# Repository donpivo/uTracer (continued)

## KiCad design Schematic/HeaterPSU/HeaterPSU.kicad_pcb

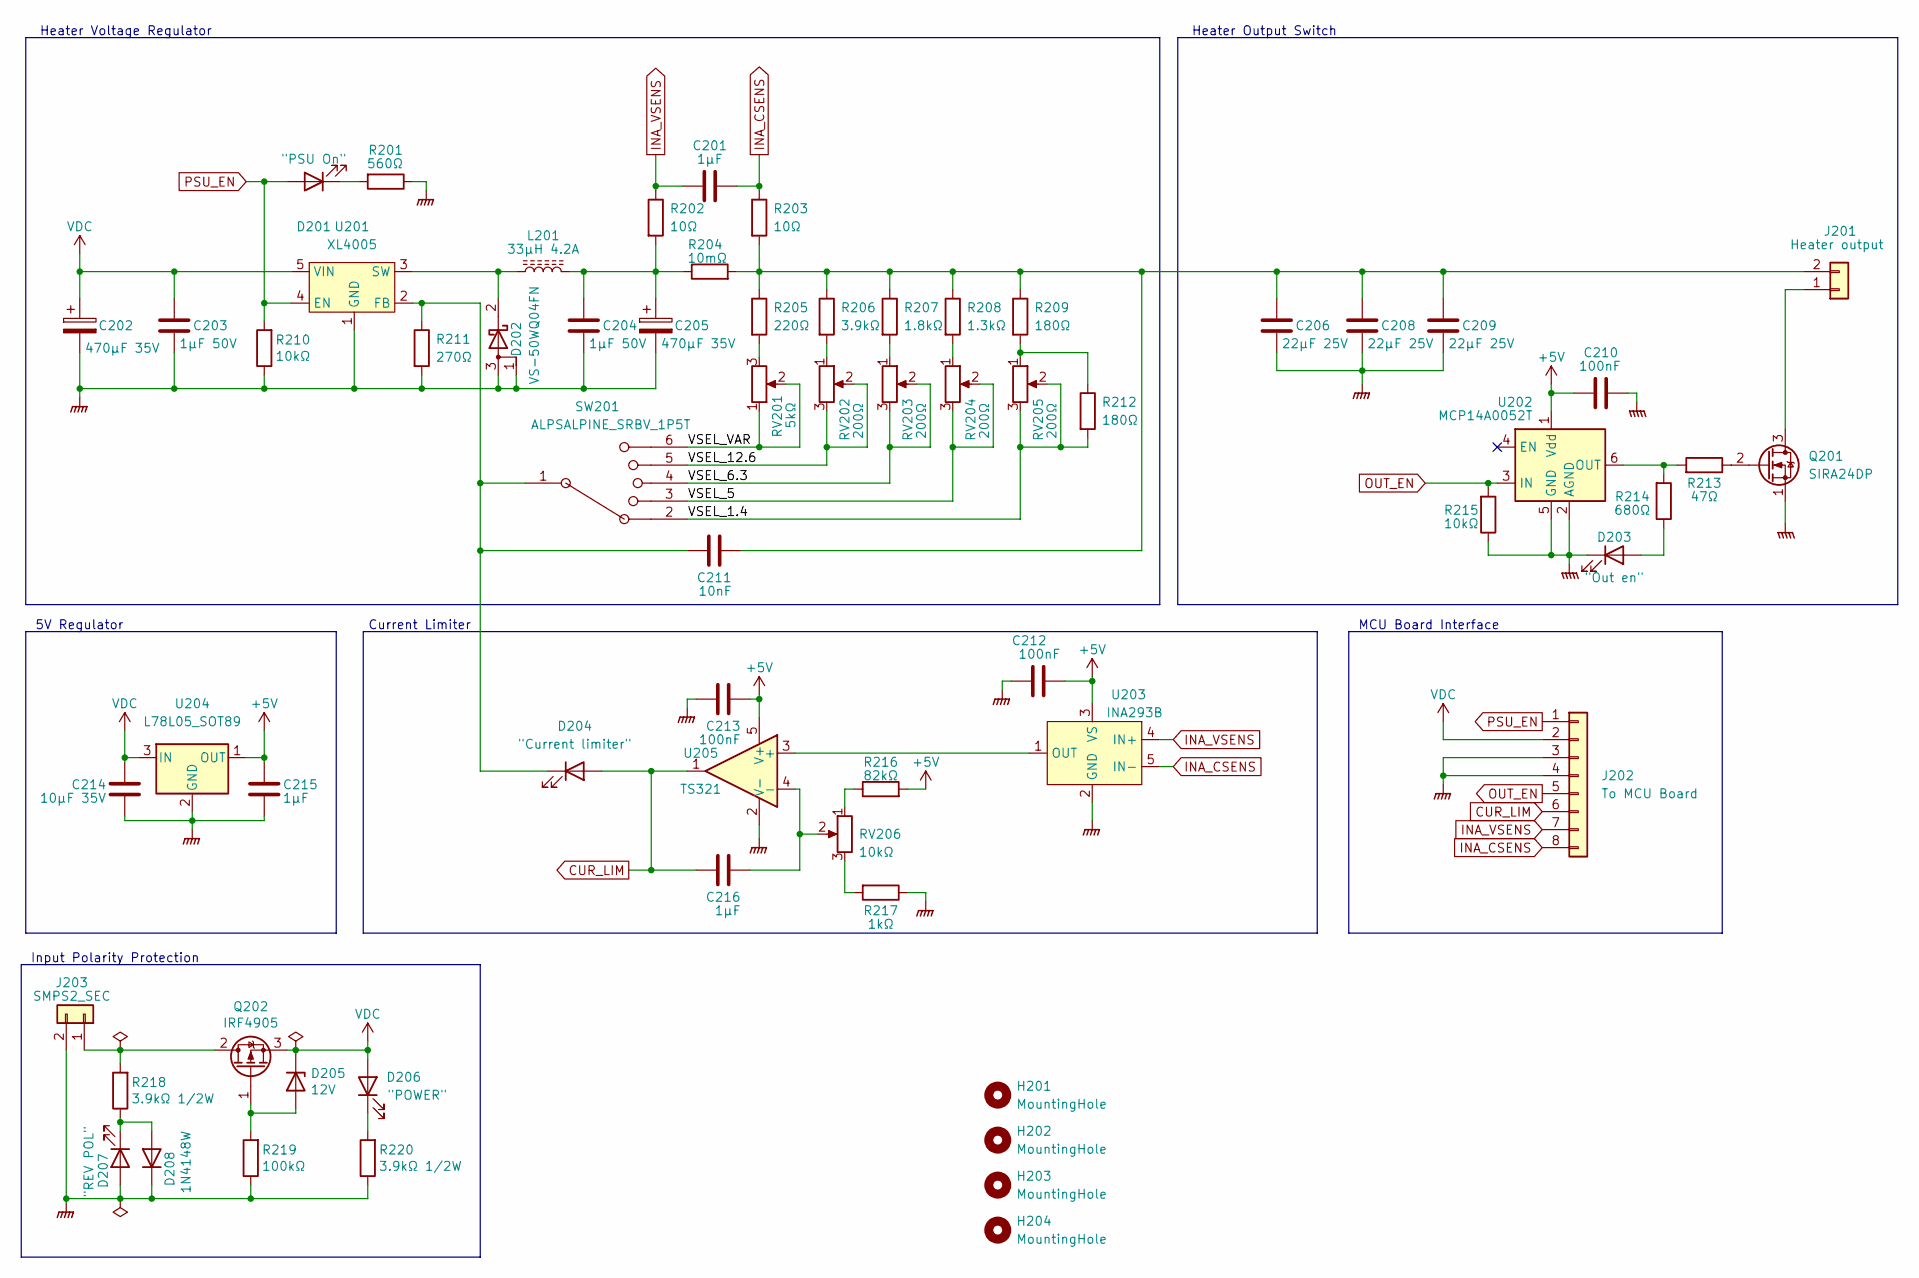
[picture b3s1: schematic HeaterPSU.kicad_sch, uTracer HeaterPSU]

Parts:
C201, C215, C216: 1µF; C_0603_1608Metric_Pad1.08x0.95mm_HandSolder
C202, C205: 470µF 35V; CP_Elec_8x10
C203, C204: 1µF 50V; C_0805_2012Metric_Pad1.18x1.45mm_HandSolder
C206, C208, C209: 22µF 25V; C_0805_2012Metric_Pad1.18x1.45mm_HandSolder
C210, C212, C213: 100nF; C_0603_1608Metric_Pad1.08x0.95mm_HandSolder
C211: 10nF; C_0805_2012Metric_Pad1.18x1.45mm_HandSolder
C214: 10µF 35V; C_0603_1608Metric_Pad1.08x0.95mm_HandSolder
D201: "PSU On"; LED_0603_1608Metric_Pad1.05x0.95mm_HandSolder
D202: VS-50WQ04FN; TO-252-2
D203: "Out en"; LED_0603_1608Metric_Pad1.05x0.95mm_HandSolder
D204: "Current limiter"; LED_0603_1608Metric_Pad1.05x0.95mm_HandSolder
D205: 12V; D_SOD-123
D206: "POWER"; LED_0603_1608Metric_Pad1.05x0.95mm_HandSolder
D207: "REV POL"; LED_0603_1608Metric_Pad1.05x0.95mm_HandSolder
D208: 1N4148W; D_SOD-123
H201, H202, H203, H204: MountingHole; MountingHole_3.2mm_M3
J201: Heater output; TerminalBlock_LCSC_P5.08mm
J202: To MCU Board; PinSocket_1x08_P2.54mm_Vertical
J203: SMPS2_SEC; TerminalBlock_LCSC_P5.08mm
L201: 33µH 4.2A; L_12x12mm_H8mm
Q201: SIRA24DP; SIRA24DP-T1-GE3
Q202: IRF4905; TO-263-2
R201: 560Ω; R_0603_1608Metric_Pad0.98x0.95mm_HandSolder
R202, R203: 10Ω; R_0805_2012Metric_Pad1.20x1.40mm_HandSolder
R204: 10mΩ; R_2512_6332Metric_Pad1.40x3.35mm_HandSolder
R205: 220Ω; R_0805_2012Metric_Pad1.20x1.40mm_HandSolder
R206: 3.9kΩ; R_0805_2012Metric_Pad1.20x1.40mm_HandSolder
R207: 1.8kΩ; R_0805_2012Metric_Pad1.20x1.40mm_HandSolder
R208: 1.3kΩ; R_0805_2012Metric_Pad1.20x1.40mm_HandSolder
R209, R212: 180Ω; R_0805_2012Metric_Pad1.20x1.40mm_HandSolder
R210: 10kΩ; R_0805_2012Metric_Pad1.20x1.40mm_HandSolder
R211: 270Ω; R_0805_2012Metric_Pad1.20x1.40mm_HandSolder
R213: 47Ω; R_0603_1608Metric_Pad0.98x0.95mm_HandSolder
R214: 680Ω; R_0603_1608Metric_Pad0.98x0.95mm_HandSolder
R215: 10kΩ; R_0603_1608Metric_Pad0.98x0.95mm_HandSolder
R216: 82kΩ; R_0603_1608Metric_Pad0.98x0.95mm_HandSolder
R217: 1kΩ; R_0603_1608Metric_Pad0.98x0.95mm_HandSolder
R218, R220: 3.9kΩ 1/2W; R_1210_3225Metric_Pad1.30x2.65mm_HandSolder
R219: 100kΩ; R_0805_2012Metric_Pad1.20x1.40mm_HandSolder
RV201: 5kΩ; Potentiometer_Bourns_PTV09A-1_Single_Vertical
RV202, RV203, RV204, RV205: 200Ω; Potentiometer_TT_35W
RV206: 10kΩ; Potentiometer_Bourns_PTV09A-1_Single_Vertical
SW201: ALPSALPINE_SRBV_1P5T; SRBV141404
U201: XL4005; TO-263-5_TabPin3
U202: MCP14A0052T; SOT-23-6_Handsoldering
U203: INA293B; SOT-23-5_HandSoldering
U204: L78L05_SOT89; SOT-89-3
U205: TS321; SOT-23-5_HandSoldering

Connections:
+5V: C210.2, C212.2, C213.2, C215.2, R216.2, U202.1 (Vdd), U203.3 (VS), U204.1 (OUT), U205.5 (V+)
/VSEL_1.4: R212.2, RV205.2, RV205.3, SW201.2
/VSEL_5: RV204.2, RV204.3, SW201.3
/VSEL_6.3: RV203.2, RV203.3, SW201.4
/VSEL_12.6: RV202.2, RV202.3, SW201.5
/VSEL_VAR: RV201.1, RV201.2, SW201.6
CUR_LIM: C216.1, D204.2 (A), J202.6, U205.1
GNDPWR: C202.2, C203.2, C204.2, C205.2, C206.2, C208.2, C209.2, C210.1, C212.1, C213.1, C214.1, C215.1, D202.1 (A), D202.3 (A), D203.1 (K), D207.2 (A), D208.1 (K), J202.3, J202.4, J203.2, Q201.1 (S), R201.1, R210.1, R211.2, R215.1, R217.1, R219.1, R220.1, U201.1 (GND), U202.2 (AGND), U202.5 (GND), U203.2 (GND), U204.2 (GND), U205.2 (V-)
INA_CSENS: C201.1, J202.8, R203.1, U203.5 (IN-)
INA_VSENS: C201.2, J202.7, R202.1, U203.4 (IN+)
unnamed: C204.1, C205.1, L201.2, R202.2, R204.1
unnamed: C211.1, D204.1 (K), R211.1, SW201.1, U201.2 (FB)
unnamed: C206.1, C208.1, C209.1, C211.2, J201.2, R203.2, R204.2, R205.1, R206.1, R207.1, R208.1, R209.1
unnamed: C216.2, RV206.2, U205.4 (-)
unnamed: D201.1 (K), R201.2
unnamed: D202.2 (K), L201.1, U201.3 (SW)
unnamed: D203.2 (A), R214.1
unnamed: D205.2 (A), Q202.1 (G), R219.2
unnamed: D206.1 (K), R220.2
unnamed: D207.1 (K), D208.2 (A), R218.1
unnamed: J201.1, Q201.3 (D)
unnamed: J203.1, Q202.2 (D), R218.2
unnamed: Q201.2 (G), R213.1
unnamed: R205.2, RV201.3
unnamed: R206.2, RV202.1
unnamed: R207.2, RV203.1
unnamed: R208.2, RV204.1
unnamed: R209.2, R212.1, RV205.1
unnamed: R213.2, R214.2, U202.6 (OUT)
unnamed: R216.1, RV206.1
unnamed: R217.2, RV206.3
unnamed: U203.1 (OUT), U205.3 (+)
OUT_EN: J202.5, R215.2, U202.3 (IN)
PSU_EN: D201.2 (A), J202.1, R210.2, U201.4 (EN)
VDC: C202.1, C203.1, C214.2, D205.1 (K), D206.2 (A), J202.2, Q202.3 (S), U201.5 (VIN), U204.3 (IN)

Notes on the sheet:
MCU Board Interface
5V Regulator
Heater Voltage Regulator
Input Polarity Protection
Current Limiter
Heater Output Switch

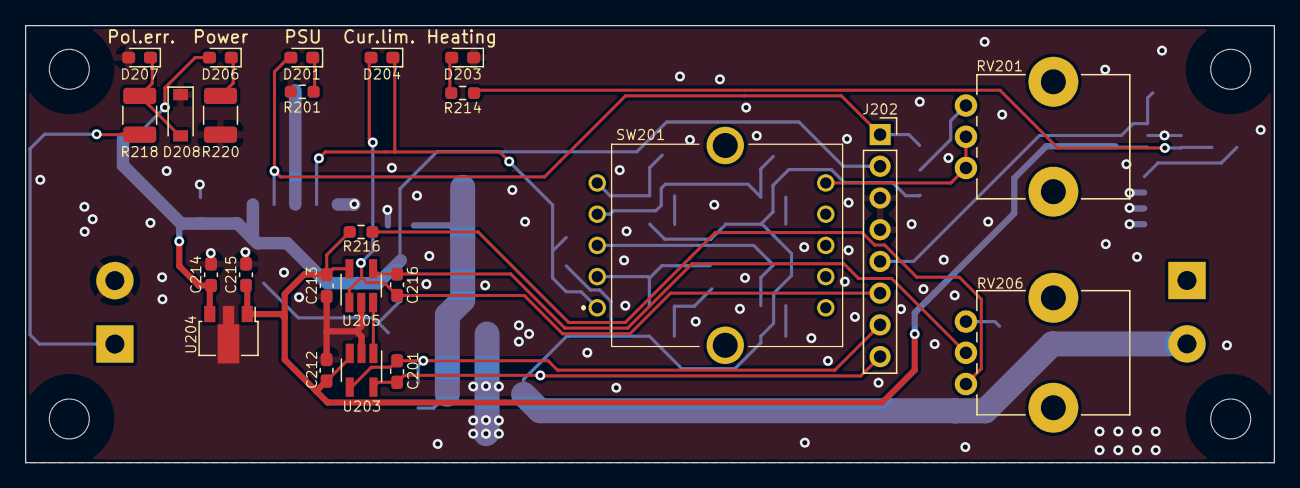
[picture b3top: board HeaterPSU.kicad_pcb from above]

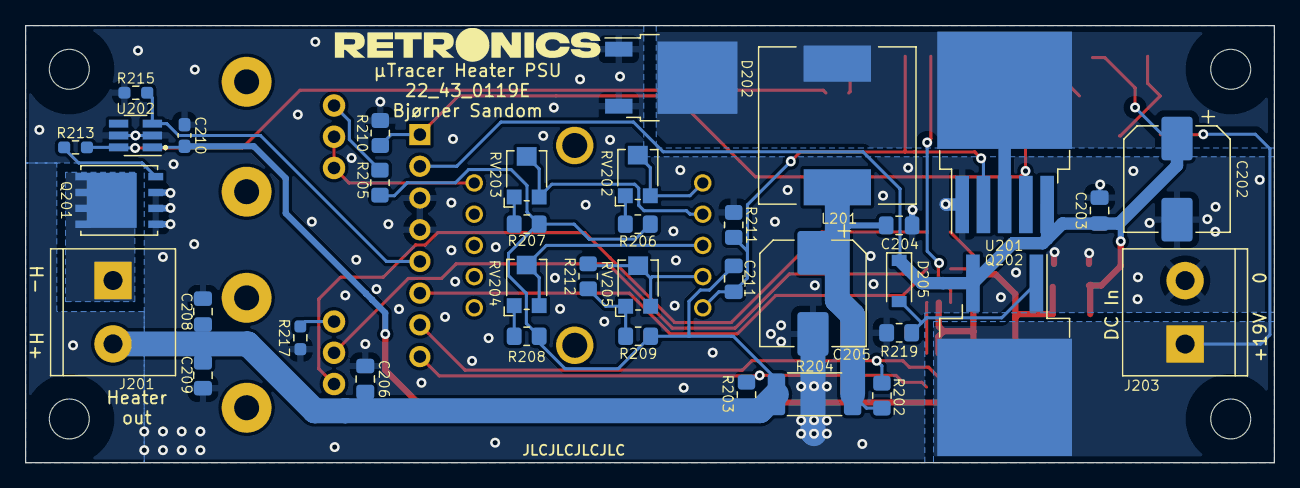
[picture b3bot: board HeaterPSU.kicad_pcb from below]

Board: 2 copper layers, 100.0 x 35.0 mm, 65 parts (37 on the bottom side), 35 nets.

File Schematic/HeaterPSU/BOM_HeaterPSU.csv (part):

"Source:","C:\Users\bjorn\OneDrive\Projects\µTracer\Schematic\HeaterPSU\HeaterPSU.kicad_sch"
"Date:","Fri May 12 07:55:15 2023"
"Tool:","Eeschema (6.0.11)"
"Generator:","C:\Program Files\KiCad\6.0\bin\scripting\plugins/bom_csv_grouped_by_value.py"
"Component Count:","65"

"Individual Components:"

"Item","Qty","Reference(s)","Value","LibPart","Footprint","Datasheet"
"","","C201","1µF","Device:C","Capacitor_SMD:C_0603_1608Metric_Pad1.08x0.95mm_HandSolder","~"
"","","C202","470µF 35V","Device:C_Polarized","Capacitor_SMD:CP_Elec_8x10","~"
"","","C203","1µF 50V","Device:C","Capacitor_SMD:C_0805_2012Metric_Pad1.18x1.45mm_HandSolder","~"
"","","C204","1µF 50V","Device:C","Capacitor_SMD:C_0805_2012Metric_Pad1.18x1.45mm_HandSolder","~"
"","","C205","470µF 35V","Device:C_Polarized","Capacitor_SMD:CP_Elec_8x10","~"
"","","C206","22µF 25V","Device:C","Capacitor_SMD:C_0805_2012Metric_Pad1.18x1.45mm_HandSolder","~"
"","","C208","22µF 25V","Device:C","Capacitor_SMD:C_0805_2012Metric_Pad1.18x1.45mm_HandSolder","~"
"","","C209","22µF 25V","Device:C","Capacitor_SMD:C_0805_2012Metric_Pad1.18x1.45mm_HandSolder","~"
"","","C210","100nF","Device:C","Capacitor_SMD:C_0603_1608Metric_Pad1.08x0.95mm_HandSolder","~"
"","","C211","10nF","Device:C","Capacitor_SMD:C_0805_2012Metric_Pad1.18x1.45mm_HandSolder","~"
"","","C212","100nF","Device:C","Capacitor_SMD:C_0603_1608Metric_Pad1.08x0.95mm_HandSolder","~"
"","","C213","100nF","Device:C","Capacitor_SMD:C_0603_1608Metric_Pad1.08x0.95mm_HandSolder","~"
"","","C214","10µF 35V","Device:C","Capacitor_SMD:C_0603_1608Metric_Pad1.08x0.95mm_HandSolder","~"
"","","C215","1µF","Device:C","Capacitor_SMD:C_0603_1608Metric_Pad1.08x0.95mm_HandSolder","~"
"","","C216","1µF","Device:C","Capacitor_SMD:C_0603_1608Metric_Pad1.08x0.95mm_HandSolder","~"
"","","D201","""PSU On""","Device:LED","LED_SMD:LED_0603_1608Metric_Pad1.05x0.95mm_HandSolder","~"
"","","D202","VS-50WQ04FN","myDevices:D_Schottky_VS-50WQ04FN","Package_TO_SOT_SMD:TO-252-2","~"
"","","D203","""Out en""","Device:LED","LED_SMD:LED_0603_1608Metric_Pad1.05x0.95mm_HandSolder","~"
"","","D204","""Current limiter""","Device:LED","LED_SMD:LED_0603_1608Metric_Pad1.05x0.95mm_HandSolder","~"
"","","D205","12V","Device:D_Zener","Diode_SMD:D_SOD-123","~"
"","","D206","""POWER""","Device:LED","LED_SMD:LED_0603_1608Metric_Pad1.05x0.95mm_HandSolder","~"
"","","D207","""REV POL""","Device:LED","LED_SMD:LED_0603_1608Metric_Pad1.05x0.95mm_HandSolder","~"
"","","D208","1N4148W","Diode:1N4148W","Diode_SMD:D_SOD-123","https://www.vishay.com/docs/85748/1n4148w.pdf"
"","","H201","MountingHole","Mechanical:MountingHole","MountingHole:MountingHole_3.2mm_M3","~"
"","","H202","MountingHole","Mechanical:MountingHole","MountingHole:MountingHole_3.2mm_M3","~"
"","","H203","MountingHole","Mechanical:MountingHole","MountingHole:MountingHole_3.2mm_M3","~"
"","","H204","MountingHole","Mechanical:MountingHole","MountingHole:MountingHole_3.2mm_M3","~"
"","","J201","Heater output","Connector_Generic:Conn_01x02","myDevices:TerminalBlock_LCSC_P5.08mm","~"
"","","J202","To MCU Board","Connector_Generic:Conn_01x08","Connector_PinSocket_2.54mm:PinSocket_1x08_P2.54mm_Vertical","~"
"","","J203","SMPS2_SEC","Connector_Generic:Conn_01x02","myDevices:TerminalBlock_LCSC_P5.08mm","~"
"","","L201","33µH 4.2A","Device:L_Ferrite","Inductor_SMD:L_12x12mm_H8mm","~"
"","","Q201","SIRA24DP","myDevices:SIRA24DP-T1-GE3","myDevices:SIRA24DP-T1-GE3",""
"","","Q202","IRF4905","Transistor_FET:IRF4905","Package_TO_SOT_SMD:TO-263-2","http://www.infineon.com/dgdl/irf4905.pdf?fileId=5546d4625336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"
"","","R201","560Ω","Device:R","Resistor_SMD:R_0603_1608Metric_Pad0.98x0.95mm_HandSolder","~"
"","","R202","10Ω","Device:R","Resistor_SMD:R_0805_2012Metric_Pad1.20x1.40mm_HandSolder","~"
"","","R203","10Ω","Device:R","Resistor_SMD:R_0805_2012Metric_Pad1.20x1.40mm_HandSolder","~"
"","","R204","10mΩ","Device:R","Resistor_SMD:R_2512_6332Metric_Pad1.40x3.35mm_HandSolder","~"
"","","R205","220Ω","Device:R","Resistor_SMD:R_0805_2012Metric_Pad1.20x1.40mm_HandSolder","~"
"","","R206","3.9kΩ","Device:R","Resistor_SMD:R_0805_2012Metric_Pad1.20x1.40mm_HandSolder","~"
"","","R207","1.8kΩ","Device:R","Resistor_SMD:R_0805_2012Metric_Pad1.20x1.40mm_HandSolder","~"
"","","R208","1.3kΩ","Device:R","Resistor_SMD:R_0805_2012Metric_Pad1.20x1.40mm_HandSolder","~"
"","","R209","180Ω","Device:R","Resistor_SMD:R_0805_2012Metric_Pad1.20x1.40mm_HandSolder","~"
"","","R210","10kΩ","Device:R","Resistor_SMD:R_0805_2012Metric_Pad1.20x1.40mm_HandSolder","~"
"","","R211","270Ω","Device:R","Resistor_SMD:R_0805_2012Metric_Pad1.20x1.40mm_HandSolder","~"
"","","R212","180Ω","Device:R","Resistor_SMD:R_0805_2012Metric_Pad1.20x1.40mm_HandSolder","~"
"","","R213","47Ω","Device:R","Resistor_SMD:R_0603_1608Metric_Pad0.98x0.95mm_HandSolder","~"
"","","R214","680Ω","Device:R","Resistor_SMD:R_0603_1608Metric_Pad0.98x0.95mm_HandSolder","~"
"","","R215","10kΩ","Device:R","Resistor_SMD:R_0603_1608Metric_Pad0.98x0.95mm_HandSolder","~"
"","","R216","91kΩ","Device:R","Resistor_SMD:R_0603_1608Metric_Pad0.98x0.95mm_HandSolder","~"
"","","R217","1kΩ","Device:R","Resistor_SMD:R_0603_1608Metric_Pad0.98x0.95mm_HandSolder","~"
"","","R218","5.6kΩ 1/2W","Device:R","Resistor_SMD:R_1210_3225Metric_Pad1.30x2.65mm_HandSolder","~"
"","","R219","100kΩ","Device:R","Resistor_SMD:R_0805_2012Metric_Pad1.20x1.40mm_HandSolder","~"
"","","R220","5.6kΩ 1/2W","Device:R","Resistor_SMD:R_1210_3225Metric_Pad1.30x2.65mm_HandSolder","~"
"","","RV201","5kΩ","Device:R_Potentiometer","Potentiometer_THT:Potentiometer_Bourns_PTV09A-1_Single_Vertical","~"
"","","RV202","200Ω","Device:R_Potentiometer","Potentiometer_SMD:Potentiometer_TT_35W","~"
"","","RV203","200Ω","Device:R_Potentiometer","Potentiometer_SMD:Potentiometer_TT_35W","~"
"","","RV204","200Ω","Device:R_Potentiometer","Potentiometer_SMD:Potentiometer_TT_35W","~"
"","","RV205","200Ω","Device:R_Potentiometer","Potentiometer_SMD:Potentiometer_TT_35W","~"
"","","RV206","10kΩ","Device:R_Potentiometer","Potentiometer_THT:Potentiometer_Bourns_PTV09A-1_Single_Vertical","~"
"","","SW201","ALPSALPINE SRBV150901","myDevices:SW_Rotary_1P5T_ALPSALPINE_SRBV","myDevices:SRBV141404",""
"","","U201","XL4005","myDevices:XL4005","Package_TO_SOT_SMD:TO-263-5_TabPin3",""
"","","U202","MCP14A0052T","myDevices:MCP14A0052T","Package_TO_SOT_SMD:SOT-23-6_Handsoldering",""
"","","U203","INA293B","myDevices:INA293B","Package_TO_SOT_SMD:SOT-23-5_HandSoldering",""
"","","U204","L78L05_SOT89","Regulator_Linear:L78L05_SOT89","Package_TO_SOT_SMD:SOT-89-3","http://www.st.com/content/ccc/resource/technical/document/da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"
"","","U205","TS321","myDevices:RS8751","Package_TO_SOT_SMD:SOT-23-5_HandSoldering",""



"Collated Components:"

"Item","Qty","Reference(s)","Value","LibPart","Footprint","Datasheet"
"1","3","C201, C215, C216","1µF","Device:C","Capacitor_SMD:C_0603_1608Metric_Pad1.08x0.95mm_HandSolder","~"
"2","2","C202, C205","470µF 35V","Device:C_Polarized","Capacitor_SMD:CP_Elec_8x10","~"
"3","2","C203, C204","1µF 50V","Device:C","Capacitor_SMD:C_0805_2012Metric_Pad1.18x1.45mm_HandSolder","~"
"4","3","C206, C208, C209","22µF 25V","Device:C","Capacitor_SMD:C_0805_2012Metric_Pad1.18x1.45mm_HandSolder","~"
"5","3","C210, C212, C213","100nF","Device:C","Capacitor_SMD:C_0603_1608Metric_Pad1.08x0.95mm_HandSolder","~"
"6","1","C211","10nF","Device:C","Capacitor_SMD:C_0805_2012Metric_Pad1.18x1.45mm_HandSolder","~"
"7","1","C214","10µF 35V","Device:C","Capacitor_SMD:C_0603_1608Metric_Pad1.08x0.95mm_HandSolder","~"
"8","1","D201","""PSU On""","Device:LED","LED_SMD:LED_0603_1608Metric_Pad1.05x0.95mm_HandSolder","~"
"9","1","D202","VS-50WQ04FN","myDevices:D_Schottky_VS-50WQ04FN","Package_TO_SOT_SMD:TO-252-2","~"
"10","1","D203","""Out en""","Device:LED","LED_SMD:LED_0603_1608Metric_Pad1.05x0.95mm_HandSolder","~"
"11","1","D204","""Current limiter""","Device:LED","LED_SMD:LED_0603_1608Metric_Pad1.05x0.95mm_HandSolder","~"
"12","1","D205","12V","Device:D_Zener","Diode_SMD:D_SOD-123","~"
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
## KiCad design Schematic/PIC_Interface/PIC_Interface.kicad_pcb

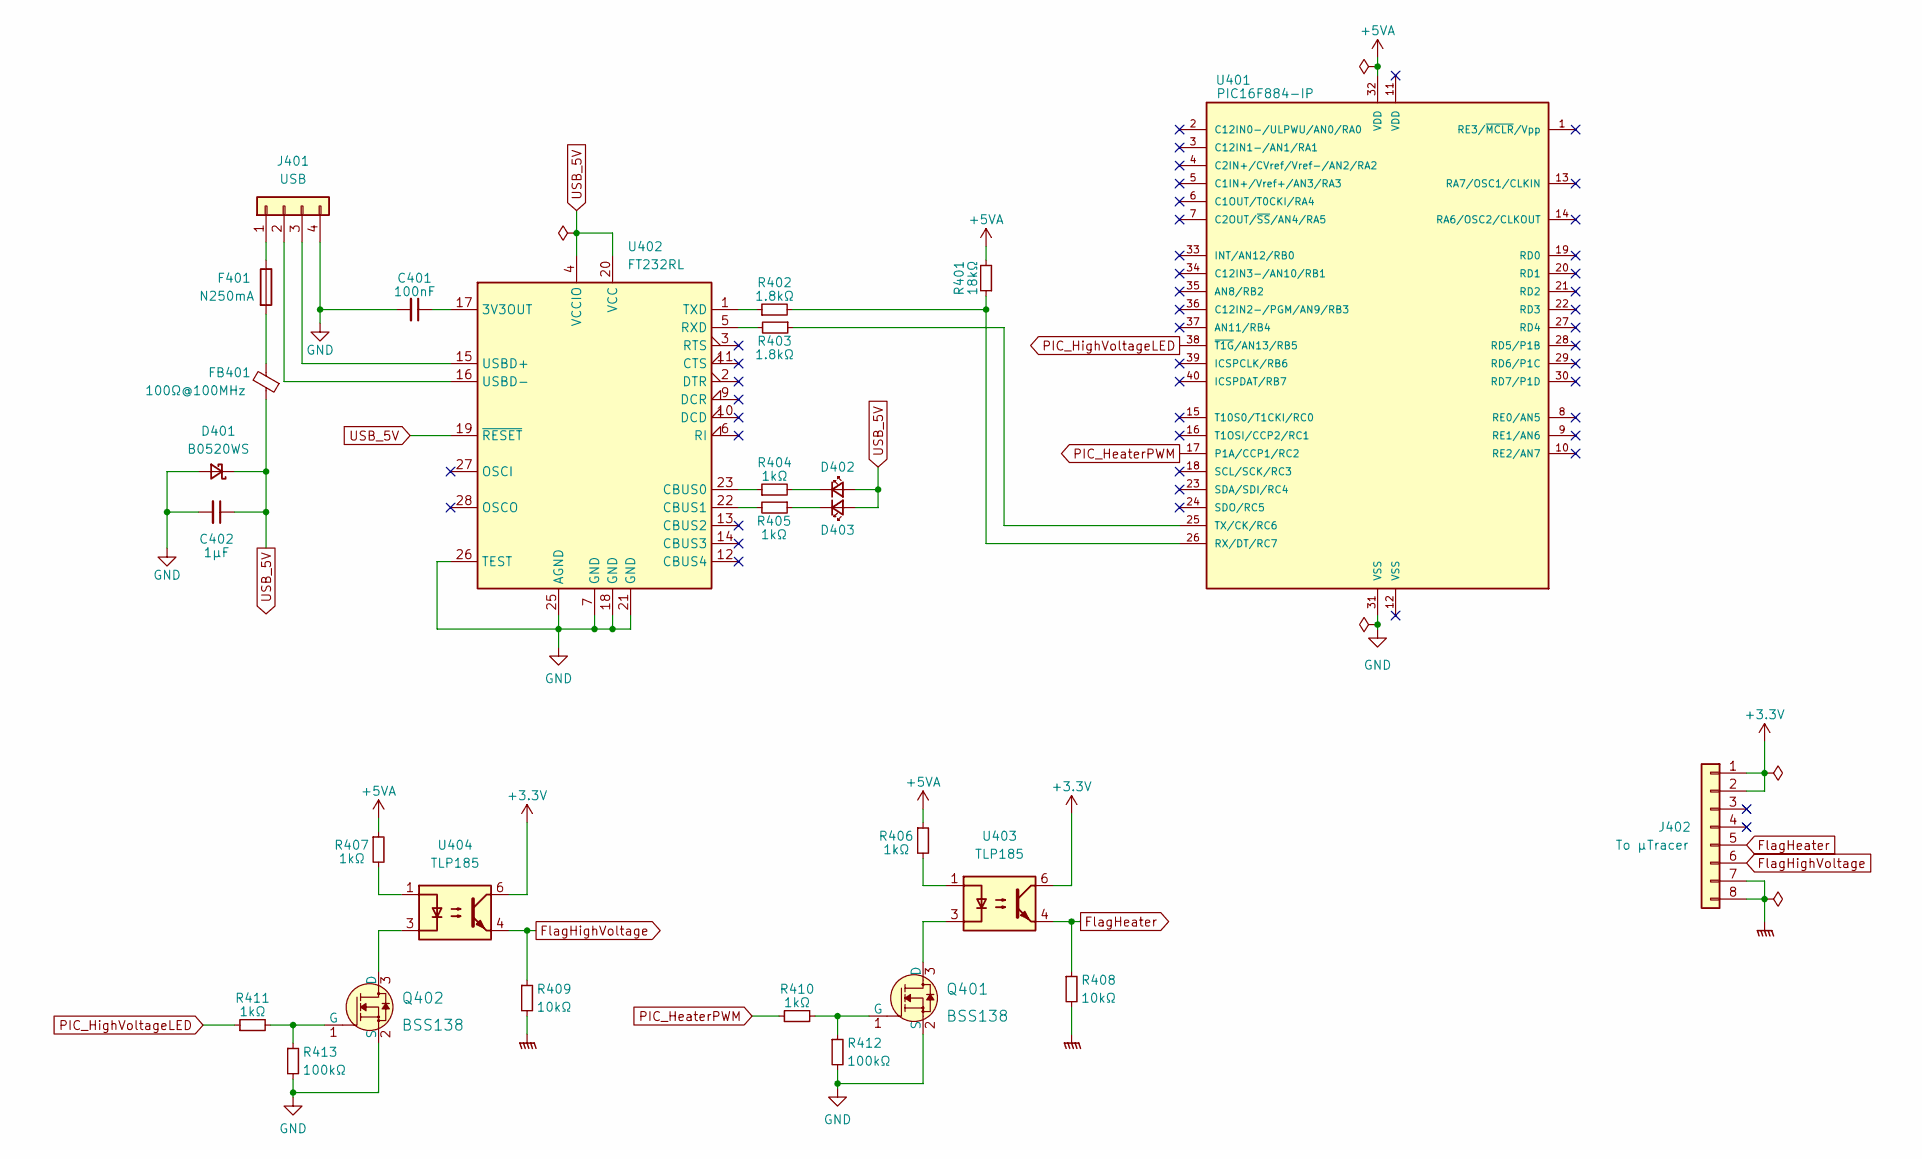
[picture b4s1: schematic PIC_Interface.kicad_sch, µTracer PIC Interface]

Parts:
C401: 100nF; C_0603_1608Metric_Pad1.08x0.95mm_HandSolder
C402: 1µF; C_0603_1608Metric_Pad1.08x0.95mm_HandSolder
D401: B0520WS; D_SOD-323_HandSoldering
D402, D403: LED_Small; LED_0603_1608Metric_Pad1.05x0.95mm_HandSolder
F401: N250mA; Fuse_1206_3216Metric_Pad1.42x1.75mm_HandSolder
FB401: 100Ω@100MHz; L_0603_1608Metric_Pad1.05x0.95mm_HandSolder
J401: USB; KF2510-4P
J402: To µTracer; 0527450897
Q401, Q402: BSS138; SOT-23-3; MPN BSS138; Digi-Key_PN BSS138CT-ND
R401: 18kΩ; R_0603_1608Metric_Pad0.98x0.95mm_HandSolder
R402, R403: 1.8kΩ; R_0603_1608Metric_Pad0.98x0.95mm_HandSolder
R404, R405, R406, R407, R410, R411: 1kΩ; R_0603_1608Metric_Pad0.98x0.95mm_HandSolder
R408, R409: 10kΩ; R_0603_1608Metric_Pad0.98x0.95mm_HandSolder
R412, R413: 100kΩ; R_0603_1608Metric_Pad0.98x0.95mm_HandSolder
U401: PIC16F884-IP; DIP-40_W15.24mm_Socket_ThroughPCB
U402: FT232RL; SSOP-28_5.3x10.2mm_P0.65mm
U403, U404: TLP185; SOIC-4_4.55x3.7mm_P2.54mm

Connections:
+3V3: J402.1, J402.2, U403.6, U404.6
+5VA: R401.2, R406.1, R407.1, U401.32 (VDD)
FlagHeater: J402.5, R408.1, U403.4
FlagHighVoltage: J402.6, R409.1, U404.4
GND: C401.2, C402.2, D401.2 (A), J401.4, Q401.2 (S), Q402.2 (S), R412.2, R413.2, U401.31 (VSS), U402.7 (GND), U402.18 (GND), U402.21 (GND), U402.25 (AGND), U402.26 (TEST)
GNDPWR: J402.7, J402.8, R408.2, R409.2
unnamed: C401.1, U402.17 (3V3OUT)
unnamed: D402.1 (K), R404.2
unnamed 8: D403.1 (K), R405.1; also elsewhere on the board
unnamed: F401.1, J401.1
unnamed: F401.2, FB401.2
unnamed: J401.2, U402.16 (USBD-)
unnamed: J401.3, U402.15 (USBD+)
unnamed: Q401.1 (G), R410.2, R412.1
unnamed: Q401.3 (D), U403.3
unnamed: Q402.1 (G), R411.2, R413.1
unnamed: Q402.3 (D), U404.3
unnamed: R401.1, R402.2, U401.26 (RX/DT/RC7)
unnamed: R402.1, U402.1 (TXD)
unnamed: R403.1, U401.25 (TX/CK/RC6)
unnamed: R403.2, U402.5 (RXD)
unnamed: R404.1, U402.23 (CBUS0)
unnamed: R405.2, U402.22 (CBUS1)
unnamed: R406.2, U403.1
unnamed: R407.2, U404.1
PIC_HeaterPWM: R410.1, U401.17 (P1A/CCP1/RC2)
PIC_HighVoltageLED: R411.1, U401.38 (~T1G/AN13/RB5)
USB_5V: C402.1, D401.1 (K), D402.2 (A), D403.2 (A), FB401.1, U402.4 (VCCIO), U402.19 (~RESET), U402.20 (VCC); also elsewhere on the board

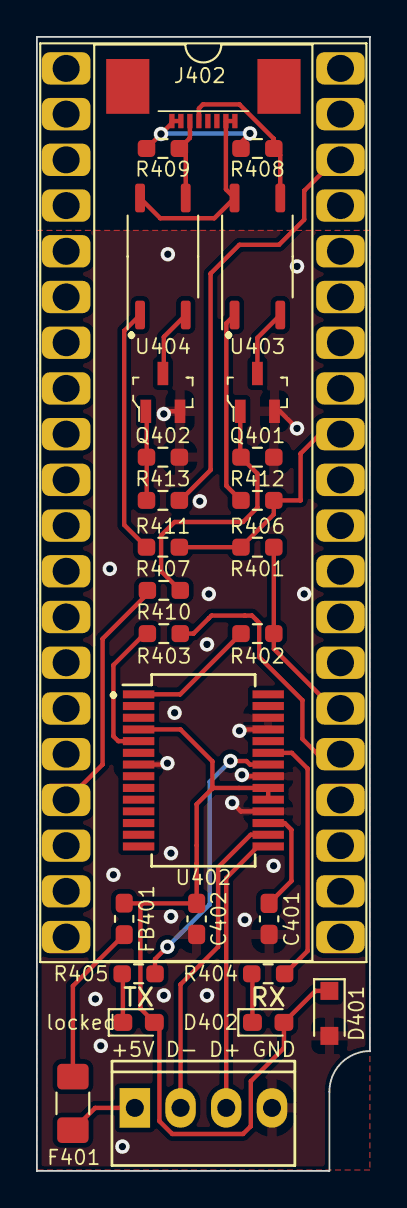
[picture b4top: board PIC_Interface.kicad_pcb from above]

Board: 2 copper layers, 18.5 x 63.0 mm, 28 parts (0 on the bottom side), 28 nets.

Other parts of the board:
locked: LED_Small; LED_0603_1608Metric_Pad1.05x0.95mm_HandSolder

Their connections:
unnamed 8: locked.1 (K); also elsewhere on the board
USB_5V: locked.2 (A); also elsewhere on the board

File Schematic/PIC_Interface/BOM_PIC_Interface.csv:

"Source:","C:\Users\bjorn\OneDrive\Projects\µTracer\Schematic\PIC_Interface\PIC_Interface.kicad_sch"
"Date:","Fri May 12 08:04:09 2023"
"Tool:","Eeschema (6.0.11)"
"Generator:","C:\Program Files\KiCad\6.0\bin\scripting\plugins/bom_csv_grouped_by_value.py"
"Component Count:","28"

"Individual Components:"

"Item","Qty","Reference(s)","Value","LibPart","Footprint","Datasheet","Category","DK_Datasheet_Link","DK_Detail_Page","Description","Digi-Key_PN","Family","MPN","Manufacturer","Status"
"","","C401","100nF","Device:C_Small","Capacitor_SMD:C_0603_1608Metric_Pad1.08x0.95mm_HandSolder","~","","","","","","","","",""
"","","C402","1µF","Device:C_Small","Capacitor_SMD:C_0603_1608Metric_Pad1.08x0.95mm_HandSolder","~","","","","","","","","",""
"","","D401","B0520WS","Device:D_Schottky_Small","Diode_SMD:D_SOD-323_HandSoldering","~","","","","","","","","",""
"","","D402","LED_Small","Device:LED_Small","LED_SMD:LED_0603_1608Metric_Pad1.05x0.95mm_HandSolder","~","","","","","","","","",""
"","","D403","LED_Small","Device:LED_Small","LED_SMD:LED_0603_1608Metric_Pad1.05x0.95mm_HandSolder","~","","","","","","","","",""
"","","F401","N250mA","Device:Fuse","Fuse:Fuse_1206_3216Metric_Pad1.42x1.75mm_HandSolder","~","","","","","","","","",""
"","","FB401","100Ω@100MHz","Device:FerriteBead_Small","Inductor_SMD:L_0603_1608Metric_Pad1.05x0.95mm_HandSolder","~","","","","","","","","",""
"","","J401","USB","Connector_Generic:Conn_01x04","myDevices:KF2510-4P","~","","","","","","","","",""
"","","J402","To heater module","Connector_Generic:Conn_01x08","myDevices:0527450897","~","","","","","","","","",""
"","","Q401","BSS138","dk_Transistors-FETs-MOSFETs-Single:BSS138","digikey-footprints:SOT-23-3","https://www.onsemi.com/pub/Collateral/BSS138-D.PDF","Discrete Semiconductor Products","https://www.onsemi.com/pub/Collateral/BSS138-D.PDF","/product-detail/en/on-semiconductor/BSS138/BSS138CT-ND/244294","MOSFET N-CH 50V 220MA SOT-23","BSS138CT-ND","Transistors - FETs, MOSFETs - Single","BSS138","ON Semiconductor","Active"
"","","Q402","BSS138","dk_Transistors-FETs-MOSFETs-Single:BSS138","digikey-footprints:SOT-23-3","https://www.onsemi.com/pub/Collateral/BSS138-D.PDF","Discrete Semiconductor Products","https://www.onsemi.com/pub/Collateral/BSS138-D.PDF","/product-detail/en/on-semiconductor/BSS138/BSS138CT-ND/244294","MOSFET N-CH 50V 220MA SOT-23","BSS138CT-ND","Transistors - FETs, MOSFETs - Single","BSS138","ON Semiconductor","Active"
"","","R401","18kΩ","Device:R_Small","Resistor_SMD:R_0603_1608Metric_Pad0.98x0.95mm_HandSolder","~","","","","","","","","",""
"","","R402","1.8kΩ","Device:R_Small","Resistor_SMD:R_0603_1608Metric_Pad0.98x0.95mm_HandSolder","~","","","","","","","","",""
"","","R403","1.8kΩ","Device:R_Small","Resistor_SMD:R_0603_1608Metric_Pad0.98x0.95mm_HandSolder","~","","","","","","","","",""
"","","R404","1kΩ","Device:R_Small","Resistor_SMD:R_0603_1608Metric_Pad0.98x0.95mm_HandSolder","~","","","","","","","","",""
"","","R405","1kΩ","Device:R_Small","Resistor_SMD:R_0603_1608Metric_Pad0.98x0.95mm_HandSolder","~","","","","","","","","",""
"","","R406","220Ω","Device:R_Small","Resistor_SMD:R_0603_1608Metric_Pad0.98x0.95mm_HandSolder","~","","","","","","","","",""
"","","R407","1kΩ","Device:R_Small","Resistor_SMD:R_0603_1608Metric_Pad0.98x0.95mm_HandSolder","~","","","","","","","","",""
"","","R408","10kΩ","Device:R_Small","Resistor_SMD:R_0603_1608Metric_Pad0.98x0.95mm_HandSolder","~","","","","","","","","",""
"","","R409","10kΩ","Device:R_Small","Resistor_SMD:R_0603_1608Metric_Pad0.98x0.95mm_HandSolder","~","","","","","","","","",""
"","","R410","1kΩ","Device:R_Small","Resistor_SMD:R_0603_1608Metric_Pad0.98x0.95mm_HandSolder","~","","","","","","","","",""
"","","R411","1kΩ","Device:R_Small","Resistor_SMD:R_0603_1608Metric_Pad0.98x0.95mm_HandSolder","~","","","","","","","","",""
"","","R412","100kΩ","Device:R_Small","Resistor_SMD:R_0603_1608Metric_Pad0.98x0.95mm_HandSolder","~","","","","","","","","",""
"","","R413","100kΩ","Device:R_Small","Resistor_SMD:R_0603_1608Metric_Pad0.98x0.95mm_HandSolder","~","","","","","","","","",""
"","","U401","Preci-dip 612-87-640-41-001101","MCU_Microchip_PIC16:PIC16F884-IP","myDevices:DIP-40_W15.24mm_Socket_ThroughPCB","https://no.mouser.com/datasheet/2/571/preci-dip_pdsad00016-2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","","","","","","","","",""
"","","U402","FT232RL","Interface_USB:FT232RL","Package_SO:SSOP-28_5.3x10.2mm_P0.65mm","https://www.ftdichip.com/Support/Documents/DataSheets/ICs/DS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","","","","","","","","",""
"","","U403","TLP185","Isolator:TLP185","Package_SO:SOIC-4_4.55x3.7mm_P2.54mm","https://toshiba.semicon-storage.com/info/docget.jsp?did=1179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","","","","","","","","",""
"","","U404","TLP185","Isolator:TLP185","Package_SO:SOIC-4_4.55x3.7mm_P2.54mm","https://toshiba.semicon-storage.com/info/docget.jsp?did=1179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","","","","","","","","",""



"Collated Components:"

"Item","Qty","Reference(s)","Value","LibPart","Footprint","Datasheet","Category","DK_Datasheet_Link","DK_Detail_Page","Description","Digi-Key_PN","Family","MPN","Manufacturer","Status"
"1","1","C401","100nF","Device:C_Small","Capacitor_SMD:C_0603_1608Metric_Pad1.08x0.95mm_HandSolder","~","","","","","","","","",""
"2","1","C402","1µF","Device:C_Small","Capacitor_SMD:C_0603_1608Metric_Pad1.08x0.95mm_HandSolder","~","","","","","","","","",""
"3","1","D401","B0520WS","Device:D_Schottky_Small","Diode_SMD:D_SOD-323_HandSoldering","~","","","","","","","","",""
"4","2","D402, D403","LED_Small","Device:LED_Small","LED_SMD:LED_0603_1608Metric_Pad1.05x0.95mm_HandSolder","~","","","","","","","","",""
"5","1","F401","N250mA","Device:Fuse","Fuse:Fuse_1206_3216Metric_Pad1.42x1.75mm_HandSolder","~","","","","","","","","",""
"6","1","FB401","100Ω@100MHz","Device:FerriteBead_Small","Inductor_SMD:L_0603_1608Metric_Pad1.05x0.95mm_HandSolder","~","","","","","","","","",""
"7","1","J401","USB","Connector_Generic:Conn_01x04","myDevices:KF2510-4P","~","","","","","","","","",""
"8","1","J402","To heater module","Connector_Generic:Conn_01x08","myDevices:0527450897","~","","","","","","","","",""
"9","2","Q401, Q402","BSS138","dk_Transistors-FETs-MOSFETs-Single:BSS138","digikey-footprints:SOT-23-3","https://www.onsemi.com/pub/Collateral/BSS138-D.PDF","Discrete Semiconductor Products","https://www.onsemi.com/pub/Collateral/BSS138-D.PDF","/product-detail/en/on-semiconductor/BSS138/BSS138CT-ND/244294","MOSFET N-CH 50V 220MA SOT-23","BSS138CT-ND","Transistors - FETs, MOSFETs - Single","BSS138","ON Semiconductor","Active"
"10","1","R401","18kΩ","Device:R_Small","Resistor_SMD:R_0603_1608Metric_Pad0.98x0.95mm_HandSolder","~","","","","","","","","",""
"11","2","R402, R403","1.8kΩ","Device:R_Small","Resistor_SMD:R_0603_1608Metric_Pad0.98x0.95mm_HandSolder","~","","","","","","","","",""
"12","5","R404, R405, R407, R410, R411","1kΩ","Device:R_Small","Resistor_SMD:R_0603_1608Metric_Pad0.98x0.95mm_HandSolder","~","","","","","","","","",""
"13","1","R406","220Ω","Device:R_Small","Resistor_SMD:R_0603_1608Metric_Pad0.98x0.95mm_HandSolder","~","","","","","","","","",""
"14","2","R408, R409","10kΩ","Device:R_Small","Resistor_SMD:R_0603_1608Metric_Pad0.98x0.95mm_HandSolder","~","","","","","","","","",""
"15","2","R412, R413","100kΩ","Device:R_Small","Resistor_SMD:R_0603_1608Metric_Pad0.98x0.95mm_HandSolder","~","","","","","","","","",""
"16","1","U401","Preci-dip 612-87-640-41-001101","MCU_Microchip_PIC16:PIC16F884-IP","myDevices:DIP-40_W15.24mm_Socket_ThroughPCB","https://no.mouser.com/datasheet/2/571/preci-dip_pdsad00016-2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","","","","","","","","",""
"17","1","U402","FT232RL","Interface_USB:FT232RL","Package_SO:SSOP-28_5.3x10.2mm_P0.65mm","https://www.ftdichip.com/Support/Documents/DataSheets/ICs/DS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","","","","","","","","",""
"18","2","U403, U404","TLP185","Isolator:TLP185","Package_SO:SOIC-4_4.55x3.7mm_P2.54mm","https://toshiba.semicon-storage.com/info/docget.jsp?did=1179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","","","","","","","","",""

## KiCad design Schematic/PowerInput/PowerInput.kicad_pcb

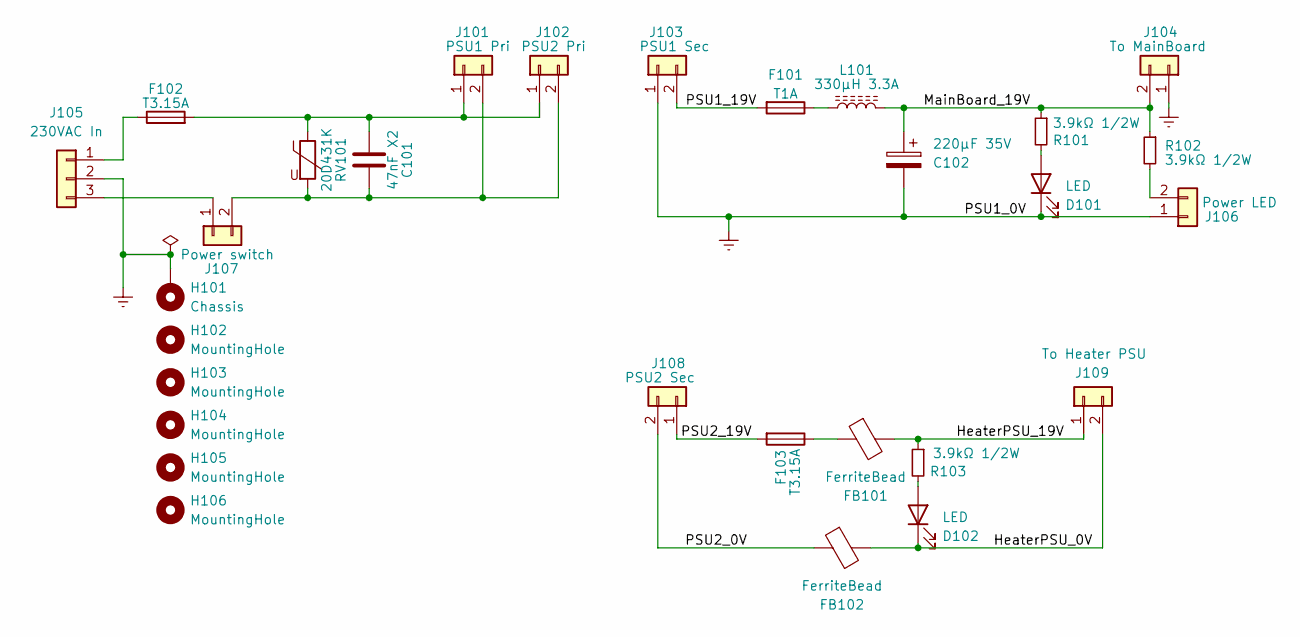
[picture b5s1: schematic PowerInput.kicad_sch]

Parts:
C101: 47nF X2; C_Rect_L13.0mm_W5.0mm_P10.00mm_FKS3_FKP3_MKS4
C102: 220µF 35V; CP_Radial_D10.0mm_P7.50mm
D101, D102: LED; LED_0805_2012Metric_Pad1.15x1.40mm_HandSolder
F101: T1A; Fuse_Littelfuse_372_D8.50mm
F102, F103: T3.15A; Fuse_Littelfuse_372_D8.50mm
FB101, FB102: FerriteBead; L_1812_4532Metric_Pad1.30x3.40mm_HandSolder
H101: Chassis; MountingHole_3.2mm_M3_Pad_Via
H102, H103, H104, H105, H106: MountingHole; MountingHole_3.2mm_M3
J101: PSU1 Pri; TerminalBlock_LCSC_P5.08mm
J102: PSU2 Pri; TerminalBlock_LCSC_P5.08mm
J103: PSU1 Sec; TerminalBlock_LCSC_P5.08mm
J104: To MainBoard; TerminalBlock_LCSC_P5.08mm
J105: 230VAC In; TerminalBlock_LCSC_P5.08mm_3
J106: Power LED; PinHeader_1x02_P2.54mm_Vertical
J107: Power switch; TerminalBlock_LCSC_P5.08mm
J108: PSU2 Sec; TerminalBlock_LCSC_P5.08mm
J109: To Heater PSU; TerminalBlock_LCSC_P5.08mm
L101: 330µH 3.3A; L_Radial_D24.4mm_P23.70mm_Murata_1400series
R101, R102, R103: 3.9kΩ 1/2W; R_1210_3225Metric_Pad1.30x2.65mm_HandSolder
RV101: 20D431K; RV_Disc_D21.5mm_W5.6mm_P10mm

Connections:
/HeaterPSU_0V: D102.1 (K), FB102.2, J109.2
/HeaterPSU_19V: FB101.2, J109.1, R103.1
/MainBoard_19V: C102.1, J104.2, L101.1, R101.1, R102.1
/PSU1_19V: F101.2, J103.2
/PSU2_0V: FB102.1, J108.2
/PSU2_19V: F103.2, J108.1
Earth: C102.2, D101.1 (K), H101.1, J103.1, J104.1, J105.2, J106.1
unnamed: C101.1, F102.2, J101.1, J102.1, RV101.1
unnamed: C101.2, J101.2, J102.2, J107.2, RV101.2
unnamed: D101.2 (A), R101.2
unnamed: D102.2 (A), R103.2
unnamed: F101.1, L101.2
unnamed: F102.1, J105.1
unnamed: F103.1, FB101.1
unnamed: J105.3, J107.1
unnamed: J106.2, R102.2

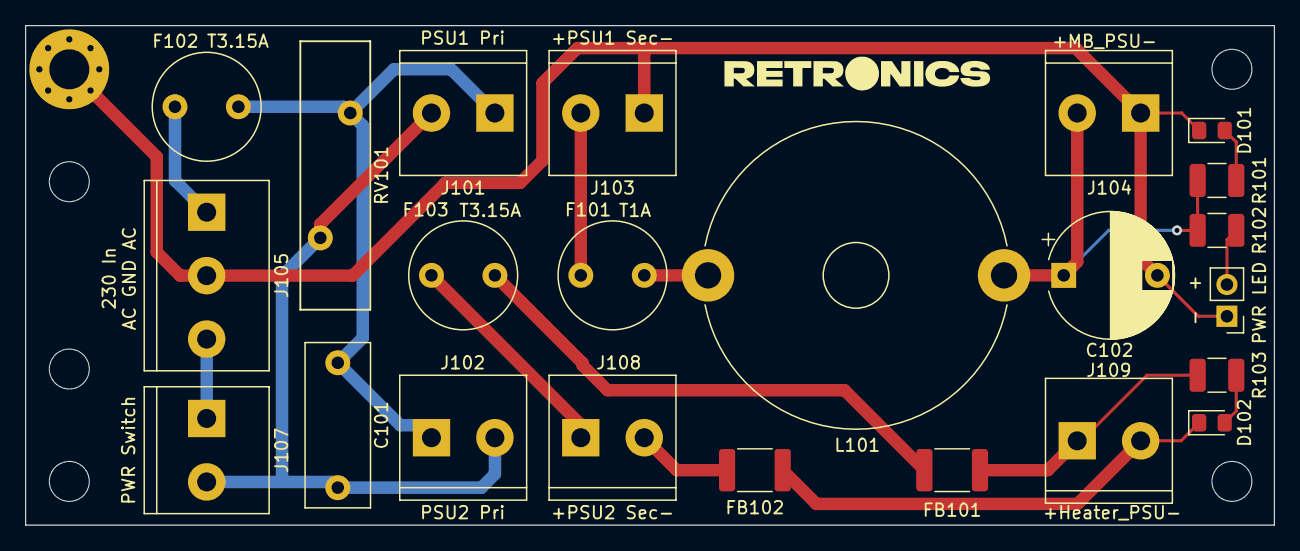
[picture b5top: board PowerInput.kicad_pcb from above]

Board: 2 copper layers, 100.0 x 40.0 mm, 29 parts (0 on the bottom side), 16 nets.
